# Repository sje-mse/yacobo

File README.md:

# yacobo
Yet Another Control Board for IBM Model M

## Inspired by Others
This project is inspired by the Model H project by John Hawthorn (https://modelh.club/)
and the LevelOneTechs Model M boards (https://level1techs.com/).
Additionally, the firmware in largely adapted from the Model H -
the only modifications are the pinouts and the keymaps, as well as some other
changes to keep it building against the tip of QMK.

## Purpose
The purpose of this project is to provide a drop-in replacement Model M control board with modern QMK firmware
that users can source, solder, and program themselves. If said goals are not important to user, they should
definitely check out the above inspirations, as those represent more complete and professional products.

## Components:
- 1x[16 Position Ribbon Connector](https://www.digikey.com/en/products/detail/te-connectivity-amp-connectors/6-520415-6/2294505)
- 1x[8 Position Ribbon Connector](https://www.digikey.com/en/products/detail/te-connectivity-amp-connectors/5-520315-8/688639)
- 1x[4 Position Ribbon Connector](https://www.digikey.com/en/products/detail/te-connectivity-amp-connectors/5-520315-4/2262309)
- 1x[USB B Connector](https://www.digikey.com/en/products/detail/on-shore-technology-inc/USB-B1HSB6/2677744)
- 3x[120 Ohm Resistor](https://www.digikey.com/en/products/detail/yageo/MFR-25FBF52-120R/9138050)
- 2x[22 Ohm Resistor](https://www.digikey.com/en/products/detail/yageo/MFR-25FBF52-22R/9138099)
- 1xBlue Pill Development Board

If your Model M membrane uses a single 12-terminal ribbon for both the matrix rows and the LEDs, use the following
part instead of the 8- and 4-Position Ribbon Connectors:

- 1x[12 Position Ribbon Connector](https://www.digikey.com/en/products/detail/te-connectivity-amp-connectors/6-520315-2/1137020)

### Corrective Resistors:
Many blue pills ship with incorrect USB D+ pullup resistances in R10. The correct resistance is 1.5 KOhm,
which should be marked `152` on the resistor. Common incorrect resistances are 10 KOhm (marked `103`),
or 4.7 KOhm (marked `472`). The `R0` spot on the Yacobo board can be populated with one of the following corrective
resistors to bring the equivalent resistence to the proper value of 1.5 KOhm:

- 10 KOhm: [1.8 KOhm](https://www.digikey.com/en/products/detail/yageo/MFR-25FTE52-1K8/13921251)
- 4.7 KOhm: [2.2 KOhm](https://www.digikey.com/en/products/detail/yageo/MFR-25FBF52-2K2/9138108)

# The Blue Pill Development Board

The Blue Pill development board houses the STM32F103C8T6, which is to be flashed with QMK firmware.
Blue Pills are very common, but can be sometimes difficult to source. One reliabe source is linked above.

The Blue Pill was chosen for three reasons:
1. It contains the STM32F103C8T6, which is supported by QMK.
2. It contains all components necessary to support the STM32F103C8T6 and presents them in an easy-to-use
   break-out through-hole board.
3. It is common and inexpensive. In these times of semiconductor shortages, thousands of pre-assembled Blue Pills
   already flood the market.

That said, the Blue Pill presents several challenges, which we will address in this README.

1. Most available Blue Pills do not ship with a bootloader that is capable of being flashed using USB.
   This can be addressed using instructions found later in this README.
2. For some reason, there are many counterfeit Blue Pills on the market. Some of these are perfectly
   functional, but others do not contain the STM32F103C8T6 they advertise, and it can be impossible to
   spot the difference while sourcing.
3. Early Blue Pills ship with an incorrect USB pullup resistor. This can be corrected by following the instructions
   found earlier in this guide.

### Selecting an Alternative
**Be careful** when selecting an alternative to the Blue Pill. Be sure that it is **pin-compatible**
with the blue pill and contains the STM32F103C8T6 chip. For reference, here is the pin diagram for the Blue Pill:

## Blue Pill Flashing Guide

Before the the yacobo firmware can be flashed to the STM32F103C8T6 on the Blue Pill, we must flash
the chip with bootloader that enables USB programming. If we have acquired a Blue Pill (or equivalent)
that already has such a bootloader, we can skip all the way down to the section labeled "Flashing the QMK Firmware".

### The Bootloader
Flashing the STM32F103C8T6 with a new bootloader requires that we procure three additional items:

- Hardware: A ST-Link V2  Emulator Downloader Programmer
- Software: STM32 ST-LINK Utility
- Firmware: The bootloader binary

#### Hardware: ST-LINK V2 Emulator Downloader/Programmer Device

Official ST-LINK V2 hardware exists, but it's expensive and overkill for our purposes.
Hobbiests use the common ST-LINK V2 Emulator Downloader/Programmer.

Much like the Blue Pill itself, the market is flooded with them. They are easy to find on Amazon, AliExpress,
Ebay, etc, and will usually run around 10 USD. These devices are often bundled with the Blue Pills themselves,
which is convenient.

The device should come with hookup wires. These wires connect the pins on the ST-LINK V2 device to the programming
pins at rear of the Blue Pill labeled `3v3`, `SWIO`, `SWCLK`, and `GND`. (The exact labels may differ by manufacturer.)

There are more than 4 pins on the ST-LINK V2 device. Fortunately, the pinouts on ST-LINK V2 are labeled.

Unfortunately, much like the Blue Pill, some ST-LINK V2 devices are a little weird, and may have inaccurate pinout
labels on their outer shell. It is easy to check this - simply pull the cover off in the direction of the USB
connector and examine the pins on the underlying circuit board:

This particular unit appears to be accurate.

#### Software: STM32 ST-LINK Utility

##### Windows
ST provides several pieces of software that are capable of programming the Blue Pill. I have had success with the
free [STSW-LINK004](https://www.st.com/en/development-tools/stsw-link004.html).

##### Linux
ST-Link V2 can be used to program Blue Pills on Linux. For Ubuntu:
```
apt install --yes stm32flash libstlink1 libstlink-dev stlink-gui stlink-tools
```

#### Firmware: The bootloader binaries

Github user rogerclarkemelbourne provides the following repo:

[STM32duino-bootloader](https://github.com/rogerclarkmelbourne/STM32duino-bootloader)

Images are provided in the `binaries` and the `bootloader_only_binaries` folders. The images in the former folder
also load a "blink" sketch onto the chips, which can be a nice way to check that the flashing process worked.

The correct bootloader binary follows the name format `generic_boot20_*.bin`, where `*` stands for the pin
designated as the status LED. This can be determined by examining the front of the blue pill board.

In the case of of this board, the correct bootloader is `generic_boot20_pc13.bin`.

#### Flashing the Bootloader

Once we have gathered the required hardware, software, and firmware, we are ready to flash the
bootloader.

**Step 0:** Boot into Windows

I would love to get the STM32CubePro software working on Linux. If anyone can get that working, please submit a PR!

**Step 1:** Connect the ST-LINK V2 Emulator Device to the Blue Pill

**Step 2:** Plug the ST-LINK V2 Emulator Device into a USB Port

Also, make sure that both the `BOOT0` and `BOOT1` jumpers are in the 0 position on the Blue Pill.

**Step 3:** Launch the STM32 ST-LINK Utility

**Step 4:** Use the `Open File` menu option to load the firmware.

**Step 5:** Connect to the ST-Link Device.

**Important:** Press the "RESET" button on the Blue Pill just before clicking Connect.
Connection must occur during a narrow boot window.

**Step 6:** Click the `Program` menu option under the `Target` menu.

**Step 7:** Click the `Start` button on the popup dialog.

**Step 8:** On completion, unplug the ST-LINK V2 Device.

The program will report that it lost connection with the target. This is normal.

**Step 9:** Use the USB-Micro port on the Blue Pill to reconnect with the host computer.
A notification may pop up about an unrecognized device. If so, press the reset button.
Eventually, Windows should report the device as a "Maple LLM 003" serial comms device.

This is an artifact of the origins of the Blue Pill. The original Blue Pills
were produced by a company named LeafLabs under the product name "Maple."
The product line was discontinued, but the knockoffs lived on in the form of the Blue Pills.

### Flashing the QMK Firmware
Now that we have a functioning bootloader, we can flash our QMK firmware onto the STM32F103C8T6 on the Blue Pill.
First, we should set up a QMK build environment. QMK is a rich and healthy project with many ways to program.

**Author's Note:**
I now direct the reader to QMK's excellent documentation for setting up their own build environment.
I got this working on Linux Mint), but I encourage you to do what works best for you.

> See the [build environment setup](https://docs.qmk.fm/#/getting_started_build_tools) and the [make instructions](https://docs.qmk.fm/#/getting_started_make_guide) for more information. Brand new to QMK? Start with our [Complete Newbs Guide](https://docs.qmk.fm/#/newbs).

**NEWS**

yacobo has been accepted into the qmk/firmware repo! It can be found in `keyboards/ibm/model_m/yacobo`.

**Step 1:** Build the desired keyboard and keymap.

Possible example command:
```
$ qmk compile -kb yacobo -km default
```

**Step 2:** Connect the Blue Pill to the host computer using the USB port

On Linux systems, you can use the `dmesg` command to check whether it has been successfully connected.

**Important**
If your Linux distribution does not recognize the Blue Pill, you may have to copy the file
`50-qmk.rules` into the proper `udev` directory.

Possible example command:
```
$ sudo cp misc/50-qmk.rules /etc/udev/rules.d
```

**Step 3:** Flash the firmware.

Possible example command:
```
$ qmk flash -kb yacobo -km default
```
Wait until the qmk starts printing out `...`, and then press the `RESET` button the Blue Pill.
This will allow the flashing to commence.

**Step 4:** Unplug and replug the Blue Pill via USB

If the flashing was successful, the os should recognize the Blue Pill as a keyboard controller!

**Author's Note:**
I recommend putting `RESET` somewhere in your keymap. That way, if you want to re-program your control board after
reassembling your Model M case, you won't have to use your socket driver to open the case again. See
`firmware/keymaps/sje/keymap.c` as an example.

**Step 5:** Complete assembly!
Remember to solder the Blue Pill with its USB Micro port facing to the right, **away** from the USB-B
port on the Yacobo PCB:

#### IMPORTANT
There is not enough room in the Model M case to accommodate a removable configuration of the
Blue Pill using standard socket headers, so the Blue Pill must be soldered directly to the PCB
via its pin headers. For this reason, it is recommended that the Blue Pill be fully programmed
before it is soldered to the PCB. That way, should the Blue Pill prove to be defective, it can
be replaced without having to desolder 40 pins. (If the Blue Pill shipped with an incorrect resistor,
it cannot be flashed with QMK via USB until the resistance is corrected. In this case,
flash the bootloader before soldering to the PCB where the resistance can be corrected.
If the bootloader successfully flashes, there is a good chance that the firmware will work as well.)

## Completion

The completed Yacobo Control Board can now be dropped right back into the case where the old one was.

**Author's Note:**
Since the Yacobo does not include the original's heavy grounding cable, a small piece of tape may be required
to keep the PCB in place if it must endure a bumpy ride somewhere.

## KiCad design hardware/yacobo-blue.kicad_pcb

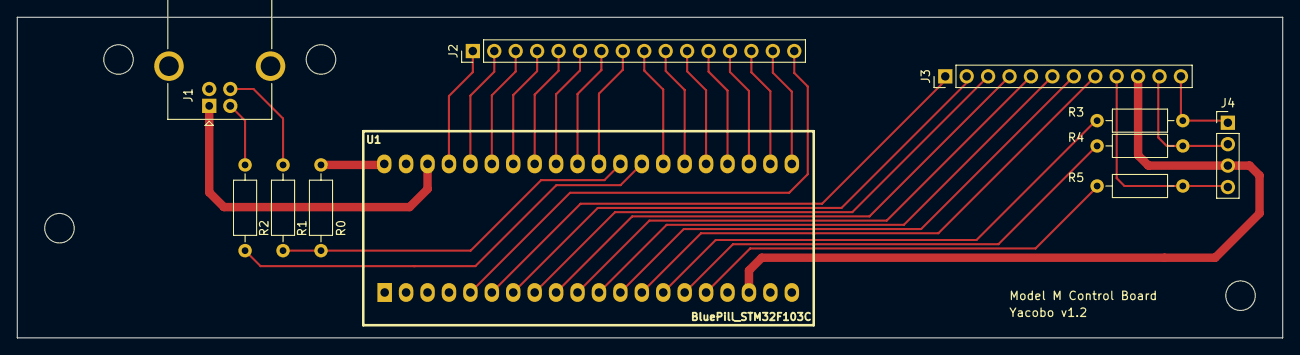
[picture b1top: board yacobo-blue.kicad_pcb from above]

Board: 2 copper layers, 150.0 x 38.0 mm, 15 parts (0 on the bottom side), 38 nets.

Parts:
J1: USB_B; USB_B_OST_USB-B1HSxx_Horizontal
J2: columns; PinHeader_1x16_P2.54mm_Vertical
J3: rows; PinHeader_1x12_P2.54mm_Vertical
J4: leds; PinHeader_1x04_P2.54mm_Vertical
M1, M2, M3, M4: MountingHole_3.5mm
R0: 1.8k; R_Axial_DIN0207_L6.3mm_D2.5mm_P10.16mm_Horizontal
R1, R2: 22; R_Axial_DIN0207_L6.3mm_D2.5mm_P10.16mm_Horizontal
R3, R4, R5: 120; R_Axial_DIN0207_L6.3mm_D2.5mm_P10.16mm_Horizontal
U1: BluePill_STM32F103C

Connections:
+3V3: J3.10, J4.3, U1.18
+5V: J1.1, U1.38
D+Pullup: R0.1, U1.40
GND: J1.4, J1.5, U1.19, U1.20, U1.39
unnamed: J1.2, R2.1
unnamed: J1.3, R1.1
unnamed: J3.9, J4.4, R5.2
unnamed: J3.11, J4.2, R4.2
unnamed: J3.12, J4.1, R3.2
USB+: R0.2, R1.2, U1.29
USB-: R2.2, U1.28
col0: J2.1, U1.37
col1: J2.2, U1.36
col2: J2.3, U1.35
col3: J2.4, U1.34
col4: J2.5, U1.33
col5: J2.6, U1.32
col6: J2.7, U1.31
col7: J2.8, U1.30
col8: J2.9, U1.27
col9: J2.10, U1.26
col10: J2.11, U1.25
col11: J2.12, U1.24
col12: J2.13, U1.23
col13: J2.14, U1.22
col14: J2.15, U1.21
col15: J2.16, U1.5
led0: R3.1, U1.14
led1: R4.1, U1.15
led2: R5.1, U1.16
row0: J3.1, U1.6
row1: J3.2, U1.7
row2: J3.3, U1.8
row3: J3.4, U1.9
row4: J3.5, U1.10
row5: J3.6, U1.11
row6: J3.7, U1.12
row7: J3.8, U1.13

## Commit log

2021-10-21 first hardware commit
2021-10-21 Create LICENSE
2021-11-08 add ground plane
2021-11-08 correct README
2021-11-08 typo
2021-11-09 add firmware
2021-11-09 update copyright
2021-11-24 add qmk rules
2021-12-02 reference qmk in the manual
2022-01-22 add reset code to keymap
2022-01-24 adding pictures
2022-01-24 correct image code
2022-01-24 use better picture for readme
2022-01-25 WIP on README updates
2022-01-25 correct pinout image
2022-01-25 add led image
2022-01-25 WIP README
2022-01-25 Bootloader flashing guide
2022-01-25 rest of the readme
2022-01-25 fix command
2022-01-25 adding missing pictures
2022-01-25 typos
2022-01-25 more typos
2022-01-25 Even more typos
2022-01-26 errata
2022-01-29 aesthetic updates on pcb traces
2022-04-22 support 12 pin configuration
2022-04-22 Readme updates
2022-04-22 more readme corrections
2022-04-22 add cad picture
2022-05-24 add new picture
2023-01-06 Changes to be in line with 0.19 qmk_firmware
2023-01-06 Updated Others' URLs
2023-01-06 [firmware] replace KC_RST with QK_BOOT (https://github.com/qmk/qmk_firmware/pull/15968)
2023-01-26 compile against latest
2024-04-24 Update README.md
    remove link to bad blue pill supplier
2024-05-30 against tip
2024-08-25 adds ST-Link V2 to README
2024-12-09 Removes firmware.
2025-05-09 space out cols vs rows. Add 3v3 top fill version.
